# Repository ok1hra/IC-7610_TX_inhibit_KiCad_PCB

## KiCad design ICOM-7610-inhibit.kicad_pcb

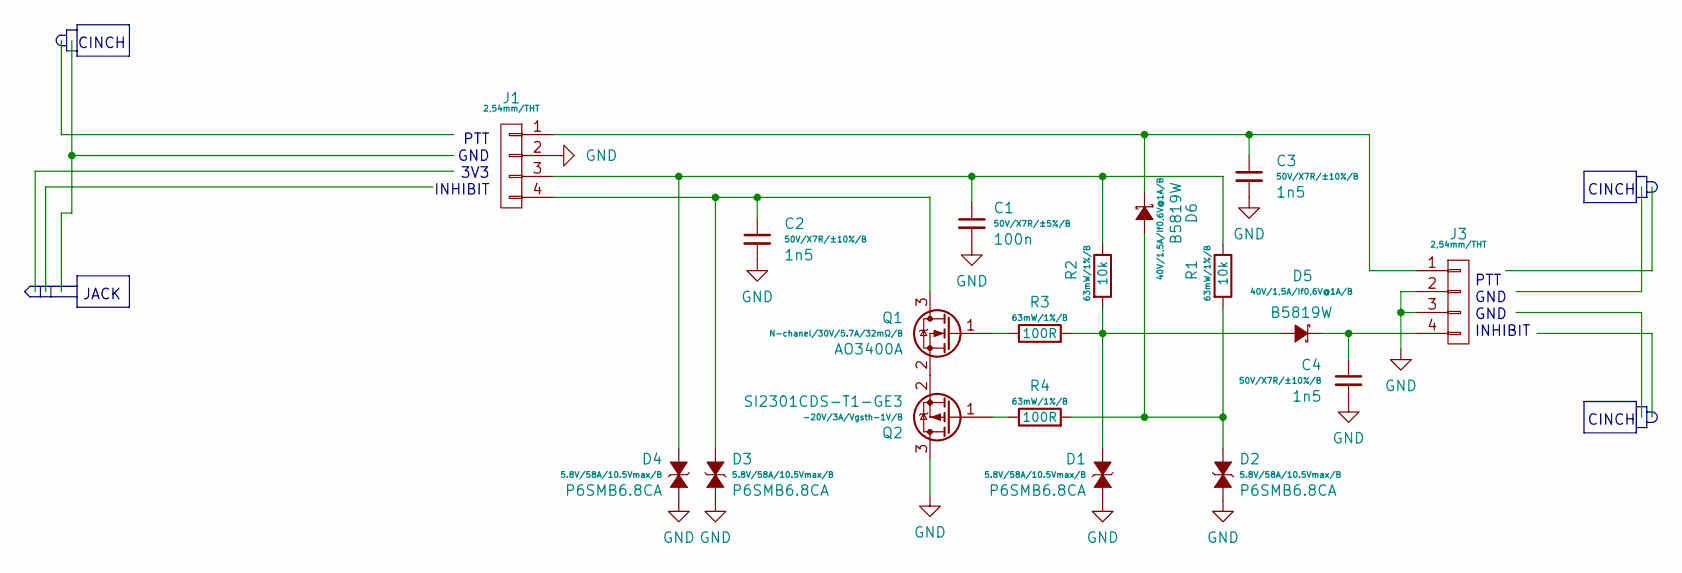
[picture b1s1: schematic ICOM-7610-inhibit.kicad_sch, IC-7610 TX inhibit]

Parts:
C1: C_100n_50V_0603; C_0603; part_value 100n; LCSC C14663
C2, C3, C4: C_1n5_50V_0603; C_0603; part_value 1n5; LCSC C1595
D1, D2, D3, D4: D_TVS-5.8V-58A_P6SMB6.8CA_SMB-DO214AA; D_SMB_Standard; part_value P6SMB6.8CA; LCSC C78395
D5, D6: D_40V-1A_B5819W_SOD123; D_SOD-123; part_value B5819W; LCSC C8598
J1, J3: Conn_01x04_PinHeaderStraight_2,54mm; Conn_PinHeaderStraight_1x04_2,54mm
Q1: NFET_30V_5.7A_AO3400A_SOT23W; SOT-23W; part_value AO3400A; LCSC C20917
Q2: PFET_-20V_3A_Si2319CDS_SOT23; SOT-23; part_value SI2301CDS-T1-GE3; LCSC C10487
R1, R2: R_10k_1%_0402; R_0402; part_value 10k; LCSC C25744
R3, R4: R_100R_1%_0402; R_0402; part_value 100R; LCSC C25076

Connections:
GND: C1.2, C2.2, C3.2, C4.2, D1.1 (K), D2.1 (K), D3.1 (K), D4.1 (K), J1.2, J3.2, J3.3, Q2.3 (D)
unnamed: D1.2 (A), D5.2 (A), R2.2, R3.2
unnamed: D2.2 (A), D6.2 (A), R1.2, R4.2
unnamed: C2.1, D3.2 (A), J1.4, Q1.3 (D)
unnamed: C1.1, D4.2 (A), J1.3, R1.1, R2.1
unnamed: C4.1, D5.1 (K), J3.4
unnamed: C3.1, D6.1 (K), J1.1, J3.1
unnamed: Q1.1 (G), R3.1
unnamed: Q1.2 (S), Q2.2 (S)
unnamed: Q2.1 (G), R4.1

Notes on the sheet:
PTT GND 3V3 INHIBIT
PTT GND GND INHIBIT
CINCH
JACK

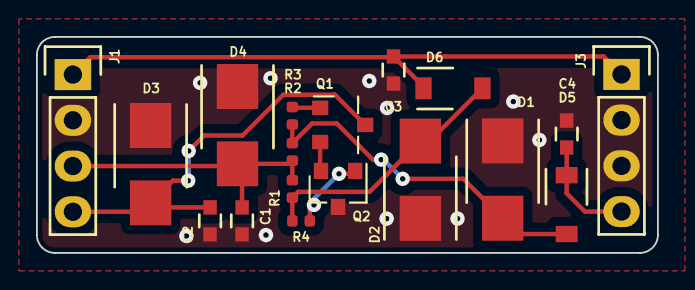
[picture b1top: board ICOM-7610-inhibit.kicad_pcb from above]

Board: 2 copper layers, 34.5 x 12.0 mm, 18 parts (0 on the bottom side), 10 nets.

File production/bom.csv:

Designator,Footprint,Quantity,Value,LCSC Part #
C1,C_0603,1,C_100n_50V_0603,C14663
"C2, C3, C4",C_0603,3,C_1n5_50V_0603,C1595
"D1, D2, D3, D4",D_SMB_Standard,4,D_TVS-5.8V-58A_P6SMB6.8CA_SMB-DO214AA,C78395
"D5, D6",D_SOD-123,2,D_40V-1A_B5819W_SOD123,C8598
"J1, J3","Conn_PinHeaderStraight_1x04_2,54mm",2,"Conn_01x04_PinHeaderStraight_2,54mm",
Q1,SOT-23W,1,NFET_30V_5.7A_AO3400A_SOT23W,C20917
Q2,SOT-23,1,PFET_-20V_3A_Si2319CDS_SOT23,C10487
"R1, R2",R_0402,2,R_10k_1%_0402,C25744
"R3, R4",R_0402,2,R_100R_1%_0402,C25076

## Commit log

2023-09-14 add simulation
